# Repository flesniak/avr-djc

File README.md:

avr-djc
=======

Firmware for self-made MIDI DJ controller using AVR µC and V-USB

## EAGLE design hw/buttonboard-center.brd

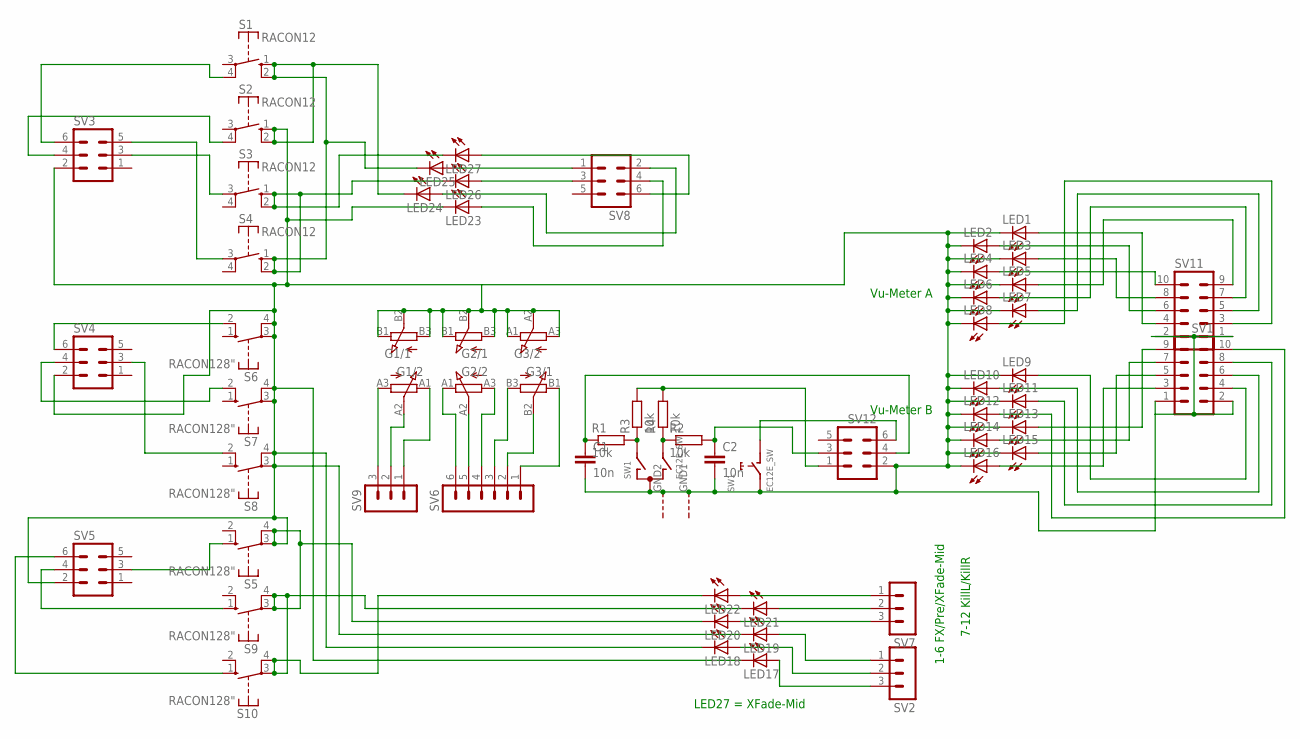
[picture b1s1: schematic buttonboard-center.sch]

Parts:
C1, C2: 10n; C025-025X050
G1, G2, G3: RS60112RS; RS60112
LED1, LED2, LED3, LED4, LED5, LED6, LED7, LED8, LED9, LED10, LED11, LED12, LED13, LED14, LED15, LED16, LED17, LED18, LED19, LED20, LED21, LED22, LED23, LED24, LED25, LED26, LED27: LED3MM
R1, R2, R3, R4: 10k; 0207/7
S1, S2, S3, S4: RACON12
S5, S6, S7, S8, S9, S10: RACON128"; RACON8
SV1, SV11: MA05-2
SV2, SV7, SV9: MA03-1
SV3, SV4, SV5, SV8, SV12: MA03-2
SV6: MA06-1
SW1: EC12E_SW; ALPS_EC12E_SW

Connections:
GND: C1.2, C2.2, G1.B1 (E), G1.B2 (S), G1.B3 (A), G2.B1 (E), G2.B2 (S), G2.B3 (A), G3.A1 (E), G3.A2 (S), G3.A3 (A), LED1.K (C), LED2.K (C), LED3.K (C), LED4.K (C), LED5.K (C), LED6.K (C), LED7.K (C), LED8.K (C), LED9.K (C), LED10.K (C), LED11.K (C), LED12.K (C), LED13.K (C), LED14.K (C), LED15.K (C), LED16.K (C), LED17.K (C), LED18.K (C), LED19.K (C), LED20.K (C), LED21.K (C), LED22.K (C), LED23.K (C), LED24.K (C), LED25.K (C), LED26.K (C), LED27.K (C), S1.1 (S), S1.2 (S), S2.1 (S), S2.2 (S), S3.1 (S), S3.2 (S), S4.1 (S), S4.2 (S), S5.3, S5.4, S6.3, S6.4, S7.3, S7.4, S8.3, S8.4, S9.3, S9.4, S10.3, S10.4, SV1.1, SV1.2, SV3.2, SV4.2, SV5.2, SV11.1, SV11.2, SV12.2, SW1.C, SW1.E (2), SW1.GND1 (G), SW1.GND2 (G)
unnamed: R1.2, R3.1, SW1.A
unnamed: LED16.A, SV1.3
unnamed: LED15.A, SV1.5
unnamed: LED14.A, SV1.7
unnamed: LED13.A, SV1.9
unnamed: LED12.A, SV1.10
unnamed: LED11.A, SV1.8
unnamed: LED10.A, SV1.6
unnamed: LED9.A, SV1.4
unnamed: LED8.A, SV11.3
unnamed: LED7.A, SV11.5
unnamed: LED6.A, SV11.7
unnamed: LED5.A, SV11.9
unnamed: LED4.A, SV11.10
unnamed: LED3.A, SV11.8
unnamed: R2.1, R4.1, SW1.B
unnamed: C1.1, R1.1, SV12.4
unnamed: LED2.A, SV11.6
unnamed: LED1.A, SV11.4
unnamed: LED17.A, SV2.3
unnamed: LED18.A, SV2.2
unnamed: LED19.A, SV2.1
unnamed: LED20.A, SV7.3
unnamed: LED21.A, SV7.2
unnamed: LED22.A, SV7.1
unnamed: LED24.A, SV8.2
unnamed: SV12.6, SW1.D (1)
unnamed: LED25.A, SV8.1
unnamed: S3.3, SV3.3
unnamed: LED23.A, SV8.4
unnamed: S2.4, SV3.4
unnamed: S1.4, SV3.6
unnamed: C2.1, R2.2, SV12.3
unnamed: R3.2, R4.2, SV12.1
unnamed: LED26.A, SV8.3
unnamed: S6.2 (S), SV4.6
unnamed: LED27.A, SV8.6
unnamed: S4.3, SV3.5
unnamed: S5.1 (S), SV5.3
unnamed: G1.A3 (A), SV9.3
unnamed: G1.A2 (S), SV9.2
unnamed: G1.A1 (E), SV9.1
unnamed: G2.A1 (E), SV6.6
unnamed: G2.A2 (S), SV6.5
unnamed: G2.A3 (A), SV6.4
unnamed: G3.B3 (A), SV6.3
unnamed: G3.B2 (S), SV6.2
unnamed: G3.B1 (E), SV6.1
unnamed: S9.1 (S), SV5.4
unnamed: S7.2 (S), SV4.4
unnamed: S8.2 (S), SV4.3
unnamed: S10.1 (S), SV5.6

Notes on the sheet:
Vu-Meter A
Vu-Meter B
LED27 = XFade-Mid
1-6 FX/Pre/XFade-Mid
7-12 KillL/KillR

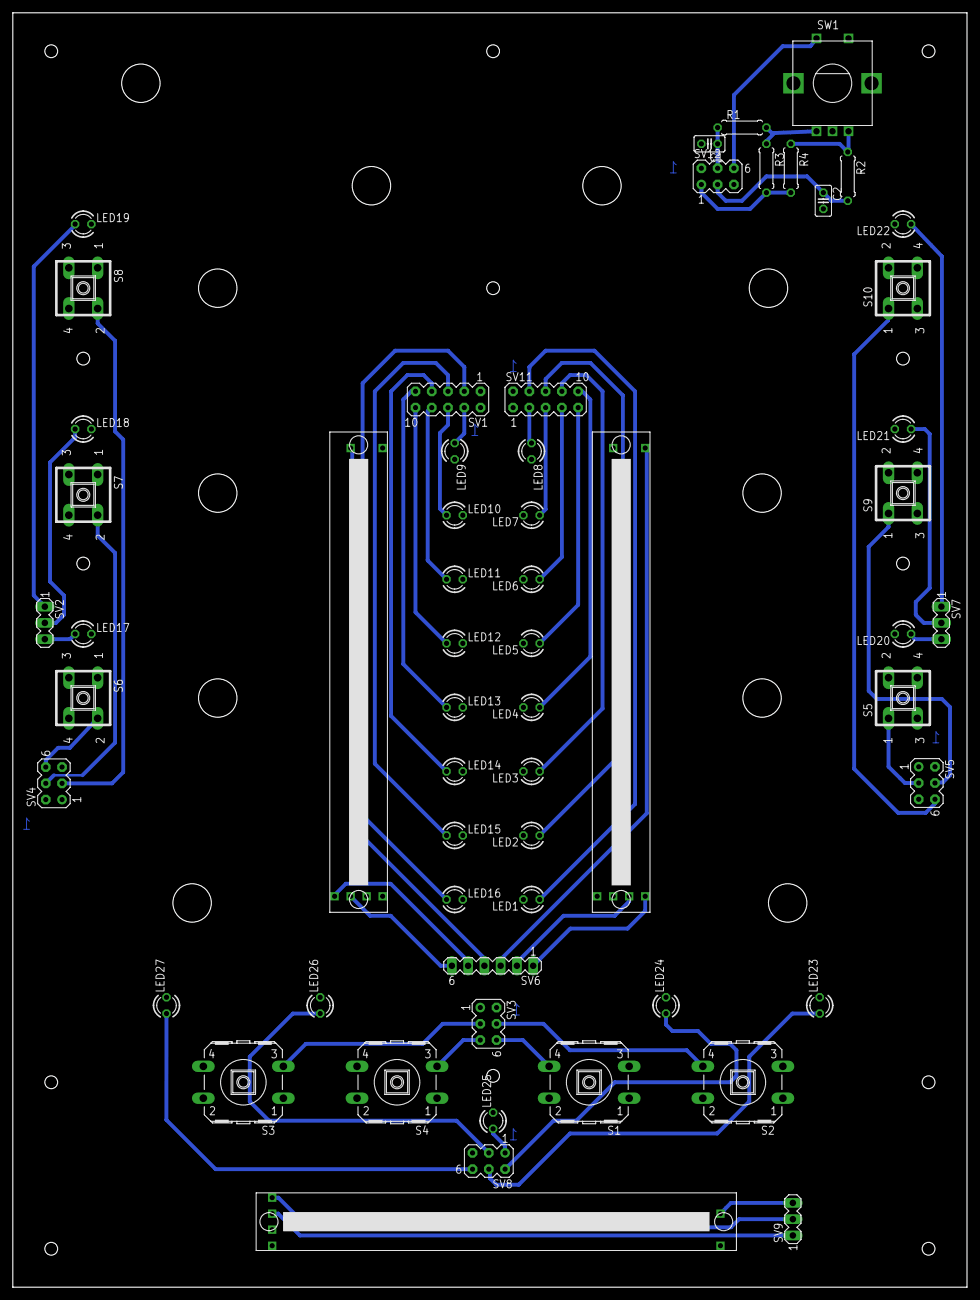
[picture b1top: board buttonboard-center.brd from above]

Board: 2 copper layers, 149.0 x 199.0 mm, 58 parts (0 on the bottom side), 53 nets.

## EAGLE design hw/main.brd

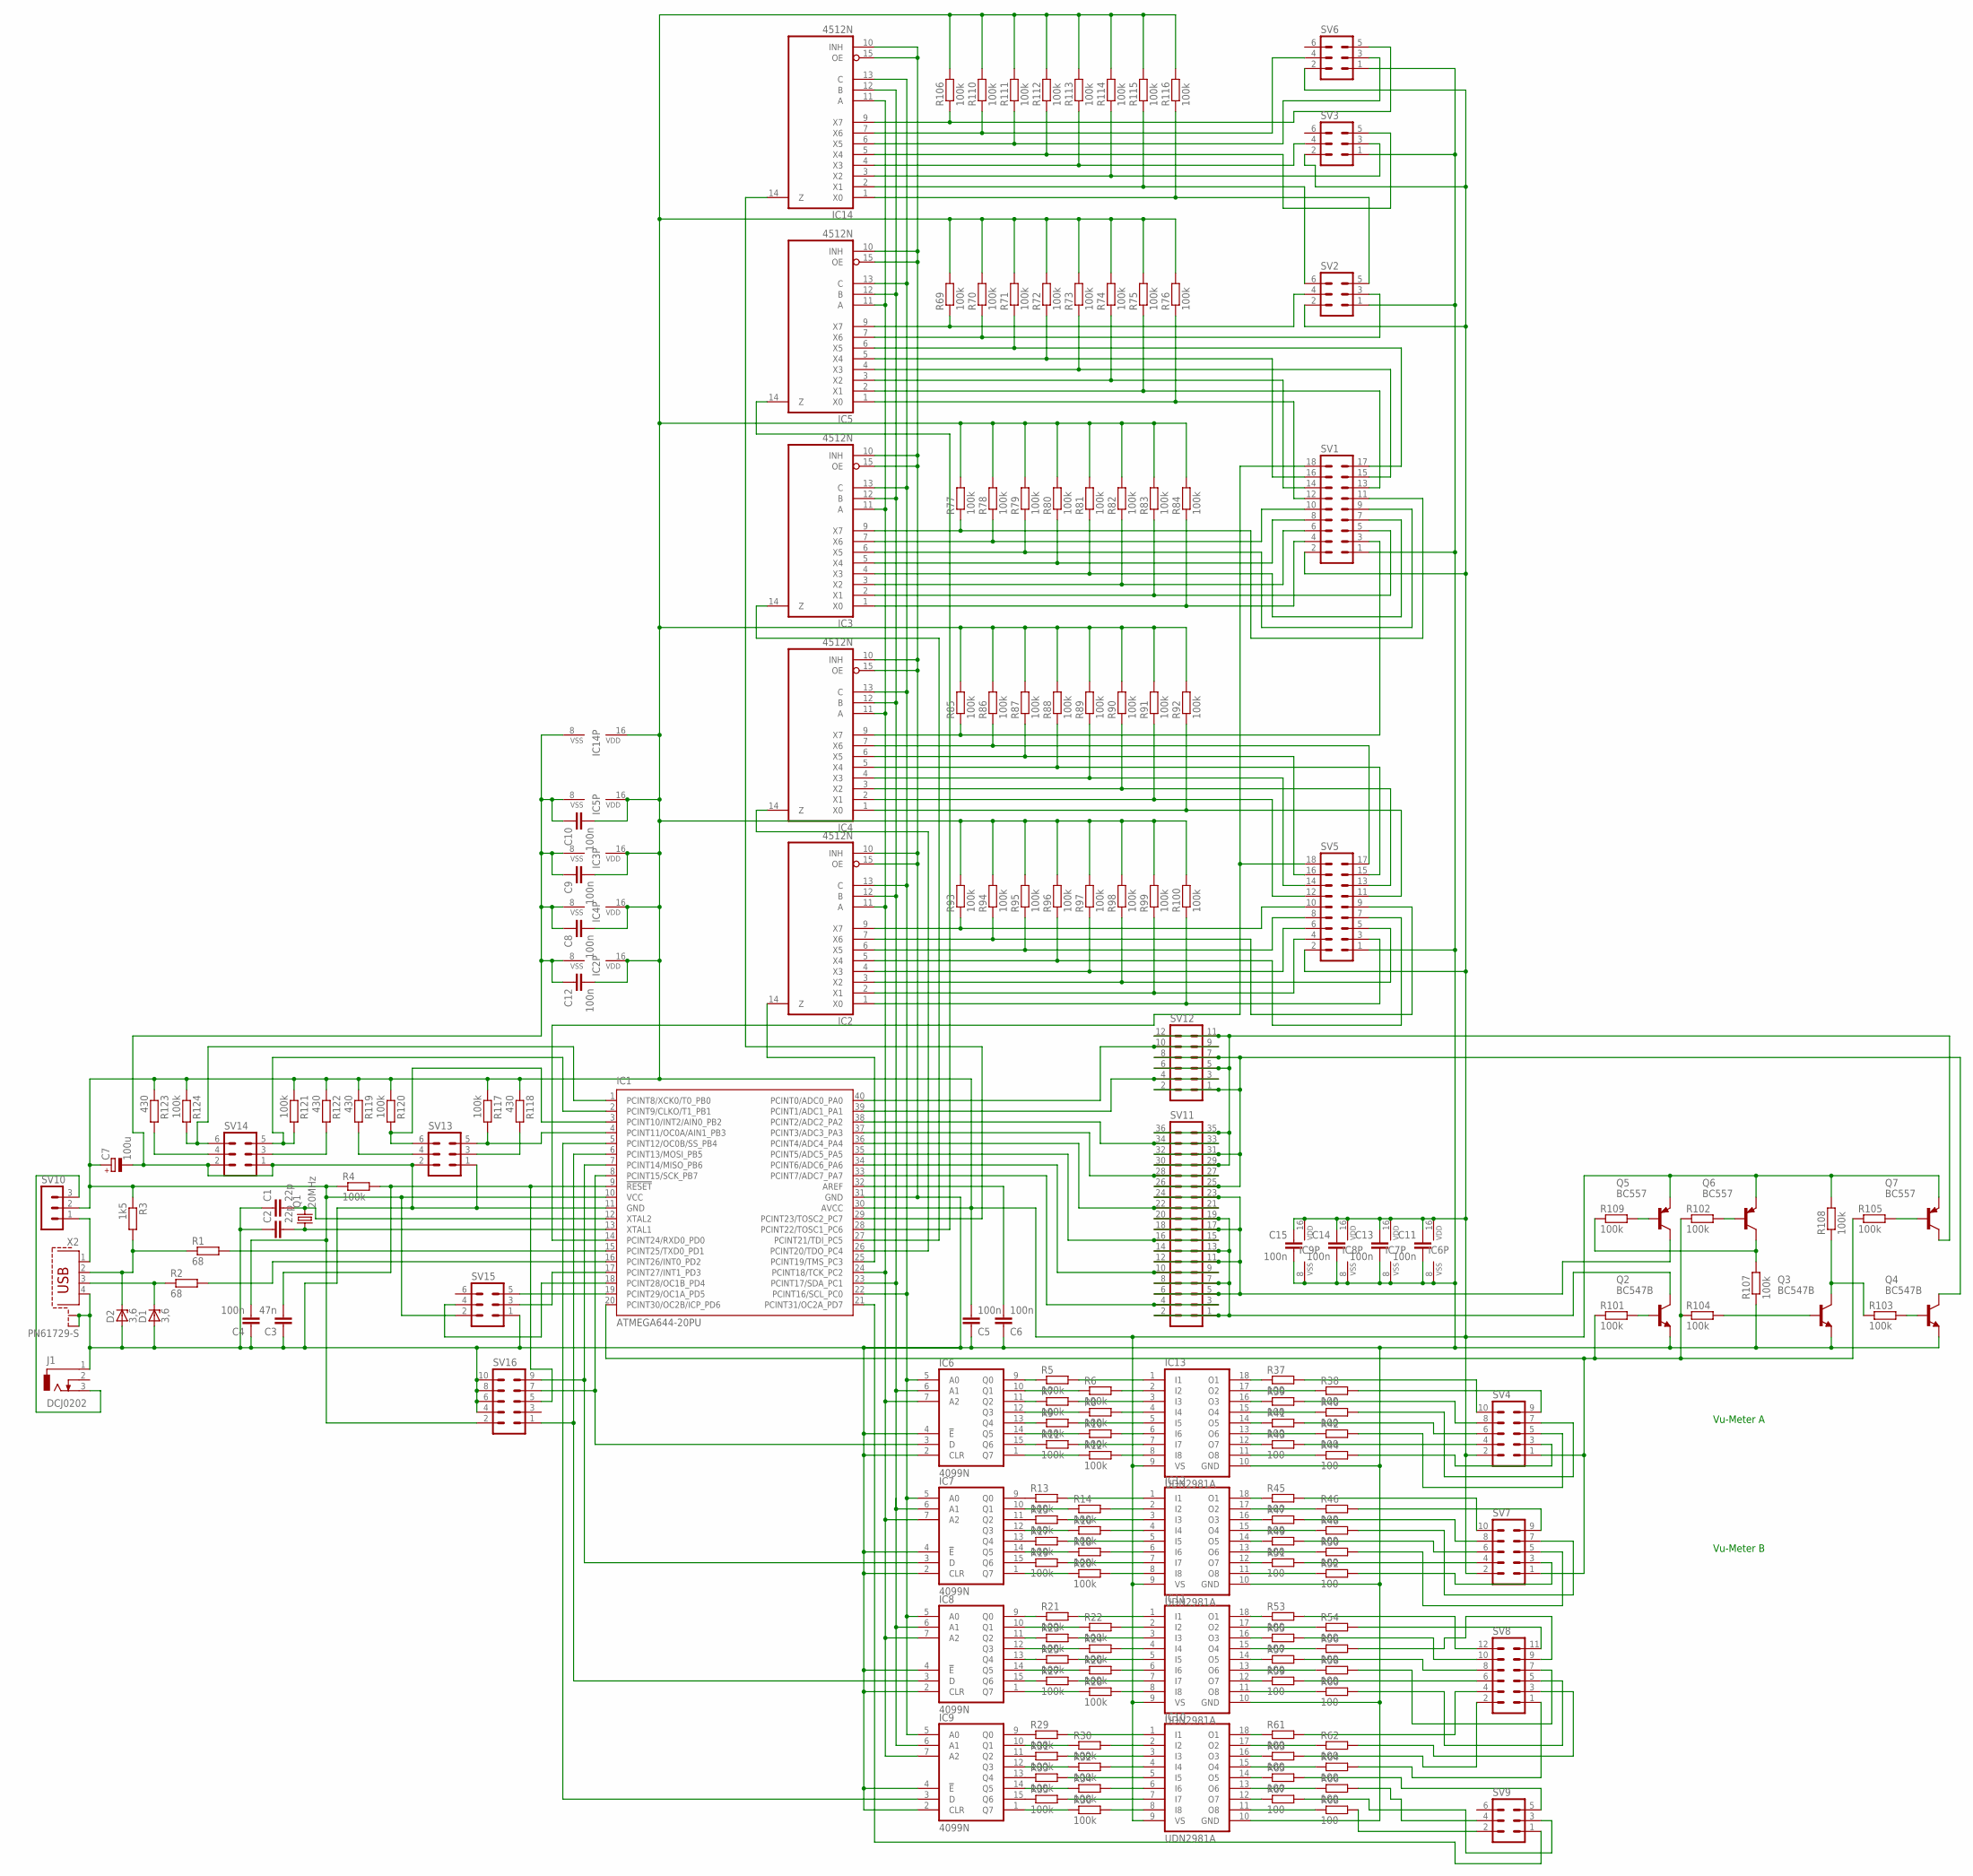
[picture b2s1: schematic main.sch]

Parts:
C1, C2: 22p; C025-024X044
C3: 47n; C025-024X044
C4, C5, C6, C8, C9, C10, C11, C12, C13, C14, C15: 100n; C025-024X044
C7: 100u; E3,5-8
D1, D2: 3,6; DO34Z7
IC1: ATMEGA644-20PU; DIL40
IC2, IC3, IC4, IC5, IC14: 4512N; DIL16
IC6, IC7, IC8, IC9: 4099N; DIL16
IC10, IC11, IC12, IC13: UDN2981A; DIL18
J1: DCJ0202
Q1: 20MHz; HC18U-V
Q2, Q3, Q4: BC547B; TO92
Q5, Q6, Q7: BC557; TO92
R1, R2: 68; 0204/7
R3: 1k5; 0204/7
R4, R5, R6, R7, R8, R9, R10, R11, R12, R13, R14, R15, R16, R17, R18, R19, R20, R21, R22, R23, R24, R25, R26, R27, R28, R29, R30, R31, R32, R33, R34, R35, R36, R69, R70, R71, R72, R73, R74, R75, R76, R77, R78, R79, R80, R81, R82, R83, R84, R85, R86, R87, R88, R89, R90, R91, R92, R93, R94, R95, R96, R97, R98, R99, R100, R101, R102, R103, R104, R105, R106, R107, R108, R109, R110, R111, R112, R113, R114, R115, R116, R117, R120, R121, R124: 100k; 0204/7
R37, R38, R39, R40, R41, R42, R43, R44, R45, R46, R47, R48, R49, R50, R51, R52, R53, R54, R55, R56, R57, R58, R59, R60, R61, R62, R63, R64, R65, R66, R67, R68: 100; 0204/7
R118, R119, R122, R123: 430; 0204/7
SV1, SV5: MA09-2
SV2, SV3, SV6, SV9, SV13, SV14, SV15: MA03-2
SV4, SV7, SV16: MA05-2
SV8, SV12: MA06-2
SV10: MA03-1
SV11: MA18-2
X2: PN61729-S

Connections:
GND: C1.1, C2.1, C3.1, C4.1, C5.1, C6.1, C7.-, C8.1, C9.1, C10.1, C11.2, C12.1, C13.2, C14.2, C15.2, D1.A, D2.A, IC1.11 (GND), IC1.31 (GND), IC2.8 (VSS), IC2.10 (INH), IC2.15 (OE), IC3.8 (VSS), IC3.10 (INH), IC3.15 (OE), IC4.8 (VSS), IC4.10 (INH), IC4.15 (OE), IC5.8 (VSS), IC5.10 (INH), IC5.15 (OE), IC6.2 (CLR), IC6.4 (!E), IC6.8 (VSS), IC7.2 (CLR), IC7.4 (!E), IC7.8 (VSS), IC8.2 (CLR), IC8.4 (!E), IC8.8 (VSS), IC9.2 (CLR), IC9.4 (!E), IC9.8 (VSS), IC10.10 (GND), IC11.10 (GND), IC12.10 (GND), IC13.10 (GND), IC14.8 (VSS), IC14.10 (INH), IC14.15 (OE), J1.1, Q2.1 (E), Q3.1 (E), Q4.1 (E), R107.1, SV1.1, SV2.1, SV3.1, SV5.1, SV6.1, SV13.1, SV13.2, SV14.1, SV14.2, SV15.1, SV16.4, SV16.6, SV16.8, SV16.10, X2.4, X2.S1, X2.S2
unnamed: IC4.9 (X7), R85.1, SV1.3
unnamed: C2.2, IC1.13 (XTAL1), Q1.1
unnamed: C1.2, IC1.12 (XTAL2), Q1.2
unnamed: IC1.14 (PCINT24/RXD0_PD0), SV1.18, SV5.18
unnamed: D1.C, R2.1, X2.3
unnamed: D2.C, R1.1, R3.2, X2.2
unnamed: IC1.16 (PCINT26/INT0_PD2), R2.2
unnamed: IC1.15 (PCINT25/TXD0_PD1), R1.2
unnamed: C3.2, IC1.9 (!RESET), R4.2, SV16.5
unnamed: IC7.9 (Q0), R13.1
unnamed: IC7.11 (Q2), R15.1
unnamed: C6.2, IC1.32 (AREF)
unnamed: IC7.13 (Q4), R17.1
unnamed: IC7.15 (Q6), R19.1
unnamed: IC1.6 (PCINT13/MOSI_PB5), IC8.3 (D), SV16.1
unnamed: IC1.5 (PCINT12/OC0B/SS_PB4), IC9.3 (D)
unnamed: IC1.23 (PCINT17/SDA_PC1), IC2.12 (B), IC3.12 (B), IC4.12 (B), IC5.12 (B), IC6.6 (A1), IC7.6 (A1), IC8.6 (A1), IC9.6 (A1), IC14.12 (B)
unnamed: IC1.22 (PCINT16/SCL_PC0), IC2.13 (C), IC3.13 (C), IC4.13 (C), IC5.13 (C), IC6.5 (A0), IC7.5 (A0), IC8.5 (A0), IC9.5 (A0), IC14.13 (C)
unnamed: IC1.24 (PCINT18/TCK_PC2), IC2.11 (A), IC3.11 (A), IC4.11 (A), IC5.11 (A), IC6.7 (A2), IC7.7 (A2), IC8.7 (A2), IC9.7 (A2), IC14.11 (A)
unnamed: IC8.9 (Q0), R21.1
unnamed: IC8.10 (Q1), R22.1
unnamed: IC8.11 (Q2), R23.1
unnamed: IC8.12 (Q3), R24.1
unnamed: IC1.27 (PCINT21/TDI_PC5), IC3.14 (Z)
unnamed: IC1.25 (PCINT19/TMS_PC3), IC2.14 (Z)
unnamed: IC3.6 (X5), R79.1, SV1.9
unnamed: IC3.9 (X7), R77.1, SV1.11
unnamed: IC12.12 (O7), R51.1
unnamed: IC8.13 (Q4), R25.1
unnamed: IC8.14 (Q5), R26.1
unnamed: IC8.15 (Q6), R27.1
unnamed: IC8.1 (Q7), R28.1
unnamed: IC13.8 (I8), R12.2
unnamed: IC13.7 (I7), R11.2
unnamed: IC13.6 (I6), R10.2
unnamed: IC13.5 (I5), R9.2
unnamed: IC13.4 (I4), R8.2
unnamed: IC13.3 (I3), R7.2
unnamed: IC13.2 (I2), R6.2
unnamed: IC13.1 (I1), R5.2
unnamed: IC10.1 (I1), R29.2
unnamed: IC10.2 (I2), R30.2
unnamed: IC10.3 (I3), R31.2
unnamed: IC10.4 (I4), R32.2
unnamed: IC10.5 (I5), R33.2
unnamed: IC10.6 (I6), R34.2
unnamed: IC10.7 (I7), R35.2
unnamed: IC10.8 (I8), R36.2
unnamed: IC9.10 (Q1), R30.1
unnamed: IC9.12 (Q3), R32.1
unnamed: IC9.14 (Q5), R34.1
unnamed: IC9.1 (Q7), R36.1
unnamed: IC11.1 (I1), R21.2
unnamed: IC9.9 (Q0), R29.1
unnamed: IC9.11 (Q2), R31.1
unnamed: IC1.28 (PCINT22/TOSC1_PC6), IC5.14 (Z)
unnamed: IC1.26 (PCINT20/TDO_PC4), IC4.14 (Z)
unnamed: IC9.13 (Q4), R33.1
unnamed: IC11.2 (I2), R22.2
unnamed: IC9.15 (Q6), R35.1
unnamed: IC11.3 (I3), R23.2
unnamed: IC11.4 (I4), R24.2
unnamed: IC1.8 (PCINT15/SCK_PB7), IC6.3 (D), SV16.7
unnamed: IC1.7 (PCINT14/MISO_PB6), IC7.3 (D), SV16.9
unnamed: IC11.5 (I5), R25.2
unnamed: IC11.6 (I6), R26.2
unnamed: IC11.7 (I7), R27.2
unnamed: IC6.9 (Q0), R5.1
unnamed: IC6.10 (Q1), R6.1
unnamed: IC6.11 (Q2), R7.1
unnamed: IC6.12 (Q3), R8.1
unnamed: IC6.13 (Q4), R9.1
unnamed: IC6.14 (Q5), R10.1
unnamed: IC6.15 (Q6), R11.1
unnamed: IC6.1 (Q7), R12.1
unnamed: IC11.8 (I8), R28.2
unnamed: IC13.18 (O1), R37.1
unnamed: IC13.17 (O2), R38.1
unnamed: R37.2, SV4.10
unnamed: R38.2, SV4.9
unnamed: IC5.9 (X7), R69.1, SV2.4
unnamed: R53.2, SV8.12
unnamed: R39.2, SV4.8
unnamed: IC12.1 (I1), R13.2
unnamed: IC12.2 (I2), R14.2
unnamed: IC12.3 (I3), R15.2
unnamed: IC12.4 (I4), R16.2
unnamed: IC12.5 (I5), R17.2
unnamed: IC12.6 (I6), R18.2
unnamed: IC12.7 (I7), R19.2
unnamed: IC12.8 (I8), R20.2
unnamed: IC7.10 (Q1), R14.1
unnamed: IC7.12 (Q3), R16.1
unnamed: IC13.16 (O3), R39.1
unnamed: IC13.15 (O4), R40.1
unnamed: R40.2, SV4.7
unnamed: R41.2, SV4.6
unnamed: IC5.6 (X5), R71.1, SV1.17
unnamed: IC7.14 (Q5), R18.1
unnamed: IC7.1 (Q7), R20.1
unnamed: IC3.4 (X3), R81.1, SV1.7
unnamed: IC13.14 (O5), R41.1
unnamed: IC13.13 (O6), R42.1
unnamed: R42.2, SV4.5
unnamed: R43.2, SV4.4
unnamed: IC5.4 (X3), R73.1, SV1.15
unnamed: IC3.2 (X1), R83.1, SV1.5
unnamed: IC13.12 (O7), R43.1
unnamed: IC13.11 (O8), R44.1
unnamed: IC12.13 (O6), R50.1
unnamed: IC5.2 (X1), R75.1, SV1.13
unnamed: R54.2, SV8.11
unnamed: IC3.3 (X2), R82.1, SV1.6
unnamed: IC12.18 (O1), R45.1
unnamed: IC12.17 (O2), R46.1
unnamed: R44.2, SV4.3
unnamed: J1.3, SV10.3
unnamed: IC12.16 (O3), R47.1
unnamed: IC12.15 (O4), R48.1
unnamed: R45.2, SV7.10
unnamed: R46.2, SV7.9
unnamed: IC12.14 (O5), R49.1
unnamed: IC11.12 (O7), R59.1
unnamed: R47.2, SV7.8
unnamed: R48.2, SV7.7
unnamed: R55.2, SV8.10
unnamed: R49.2, SV7.6
unnamed: R50.2, SV7.5
unnamed: IC12.11 (O8), R52.1
unnamed: R51.2, SV7.4
unnamed: IC11.18 (O1), R53.1
unnamed: IC11.17 (O2), R54.1
unnamed: R52.2, SV7.3
unnamed: IC5.7 (X6), R70.1, SV2.3
unnamed: IC11.16 (O3), R55.1
unnamed: IC11.15 (O4), R56.1
unnamed: IC1.33 (PCINT7/ADC7_PA7), SV11.3, SV11.4
unnamed: IC3.1 (X0), R84.1, SV1.4
unnamed: IC11.14 (O5), R57.1
unnamed: IC11.13 (O6), R58.1
unnamed: R56.2, SV8.9
unnamed: R57.2, SV8.8
unnamed: R58.2, SV8.7
unnamed: R59.2, SV8.6
unnamed: R60.2, SV8.5
unnamed: IC11.11 (O8), R60.1
unnamed: R61.2, SV8.4
unnamed: IC10.18 (O1), R61.1
unnamed: IC10.17 (O2), R62.1
unnamed: R62.2, SV8.3
unnamed: IC1.34 (PCINT6/ADC6_PA6), SV11.9, SV11.10
unnamed: IC10.16 (O3), R63.1
unnamed: IC10.15 (O4), R64.1
unnamed: IC4.7 (X6), R86.1, SV5.17
unnamed: IC4.6 (X5), R87.1, SV5.16
unnamed: IC10.14 (O5), R65.1
unnamed: IC10.13 (O6), R66.1
unnamed: IC4.5 (X4), R88.1, SV5.15
unnamed: IC4.4 (X3), R89.1, SV5.14
unnamed: IC10.12 (O7), R67.1
unnamed: IC4.3 (X2), R90.1, SV5.13
unnamed: IC1.29 (PCINT23/TOSC2_PC7), IC14.14 (Z)
unnamed: IC10.11 (O8), R68.1
unnamed: IC5.5 (X4), R72.1, SV1.16
unnamed: IC4.2 (X1), R91.1, SV5.12
unnamed: R63.2, SV8.2
unnamed: IC4.1 (X0), R92.1, SV5.11
unnamed: IC2.9 (X7), R93.1, SV5.10
unnamed: IC2.7 (X6), R94.1, SV5.9
unnamed: IC2.6 (X5), R95.1, SV5.8
unnamed: IC14.9 (X7), R106.1, SV6.5
unnamed: IC2.5 (X4), R96.1, SV5.7
unnamed: IC14.7 (X6), R110.1, SV6.4
unnamed: IC14.6 (X5), R111.1, SV6.3
unnamed: IC14.4 (X3), R113.1, SV3.4
unnamed: IC14.2 (X1), R115.1, SV2.6
unnamed: IC2.4 (X3), R97.1, SV5.6
unnamed: IC2.3 (X2), R98.1, SV5.5
unnamed: R64.2, SV8.1
unnamed: IC2.2 (X1), R99.1, SV5.4
unnamed: R65.2, SV9.5
unnamed: IC2.1 (X0), R100.1, SV5.3
unnamed: R66.2, SV9.4
unnamed: IC3.7 (X6), R78.1, SV1.10
unnamed: IC1.20 (PCINT30/OC2B/ICP_PD6), R101.1, R102.1, R104.1, R105.1, SV4.1, SV7.1
unnamed: Q6.2 (B), R102.2
unnamed: R67.2, SV9.3
unnamed: IC14.5 (X4), R112.1, SV3.5
unnamed: Q7.2 (B), R105.2
unnamed: IC14.3 (X2), R114.1, SV3.3
unnamed: IC14.1 (X0), R116.1, SV2.5
unnamed: Q2.2 (B), R101.2
unnamed: R68.2, SV9.2
unnamed: IC3.5 (X4), R80.1, SV1.8
unnamed: Q3.2 (B), R104.2
unnamed: Q6.3 (C), R107.2, R109.1
unnamed: Q3.3 (C), R103.1, R108.1
unnamed: Q4.2 (B), R103.2
unnamed: Q5.2 (B), R109.2
unnamed: IC1.21 (PCINT31/OC2A_PD7), SV9.1
unnamed: IC1.4 (PCINT11/OC0A/AIN1_PB3), R117.2, SV13.5
unnamed: R118.2, SV13.3
unnamed: IC1.3 (PCINT10/INT2/AIN0_PB2), R120.2, SV13.6
unnamed: IC1.35 (PCINT5/ADC5_PA5), SV11.15, SV11.16
unnamed: R119.2, SV13.4
unnamed: IC1.2 (PCINT9/CLKO/T1_PB1), R121.2, SV14.5
unnamed: R122.2, SV14.3
unnamed: IC1.1 (PCINT8/XCK0/T0_PB0), R124.2, SV14.6
unnamed: SV10.1, X2.1
unnamed: IC1.36 (PCINT4/ADC4_PA4), SV11.21, SV11.22
unnamed: IC1.37 (PCINT3/ADC3_PA3), SV11.27, SV11.28
unnamed: R123.2, SV14.4
unnamed: IC1.38 (PCINT2/ADC2_PA2), SV11.33, SV11.34
unnamed: IC5.3 (X2), R74.1, SV1.14
unnamed: IC1.39 (PCINT1/ADC1_PA1), SV12.3, SV12.4
unnamed: IC5.1 (X0), R76.1, SV1.12
unnamed: IC1.40 (PCINT0/ADC0_PA0), SV12.9, SV12.10
unnamed: Q4.3 (C), SV11.25, SV11.26, SV11.31, SV11.32, SV12.1, SV12.2, SV12.7, SV12.8
unnamed: IC1.18 (PCINT28/OC1B_PD4), SV15.4
unnamed: IC1.19 (PCINT29/OC1A_PD5), SV15.5
unnamed: IC1.17 (PCINT27/INT1_PD3), SV15.3
unnamed: Q5.3 (C), SV11.5, SV11.6, SV11.11, SV11.12, SV11.17, SV11.18, SV11.23, SV11.24
unnamed: Q2.3 (C), SV11.1, SV11.2, SV11.7, SV11.8, SV11.13, SV11.14, SV11.19, SV11.20
unnamed: Q7.3 (C), SV11.29, SV11.30, SV11.35, SV11.36, SV12.5, SV12.6, SV12.11, SV12.12
VCC: C4.2, C5.2, C7.+, C8.2, C9.2, C10.2, C11.1, C12.2, C13.1, C14.1, C15.1, IC1.10 (VCC), IC1.30 (AVCC), IC2.16 (VDD), IC3.16 (VDD), IC4.16 (VDD), IC5.16 (VDD), IC6.16 (VDD), IC7.16 (VDD), IC8.16 (VDD), IC9.16 (VDD), IC10.9 (VS), IC11.9 (VS), IC12.9 (VS), IC13.9 (VS), IC14.16 (VDD), Q5.1 (E), Q6.1 (E), Q7.1 (E), R3.1, R4.1, R69.2, R70.2, R71.2, R72.2, R73.2, R74.2, R75.2, R76.2, R77.2, R78.2, R79.2, R80.2, R81.2, R82.2, R83.2, R84.2, R85.2, R86.2, R87.2, R88.2, R89.2, R90.2, R91.2, R92.2, R93.2, R94.2, R95.2, R96.2, R97.2, R98.2, R99.2, R100.2, R106.2, R108.2, R110.2, R111.2, R112.2, R113.2, R114.2, R115.2, R116.2, R117.1, R118.1, R119.1, R120.1, R121.1, R122.1, R123.1, R124.1, SV1.2, SV2.2, SV3.2, SV4.2, SV5.2, SV6.2, SV7.2, SV10.2, SV15.2, SV16.2

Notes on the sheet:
Vu-Meter A
Vu-Meter B

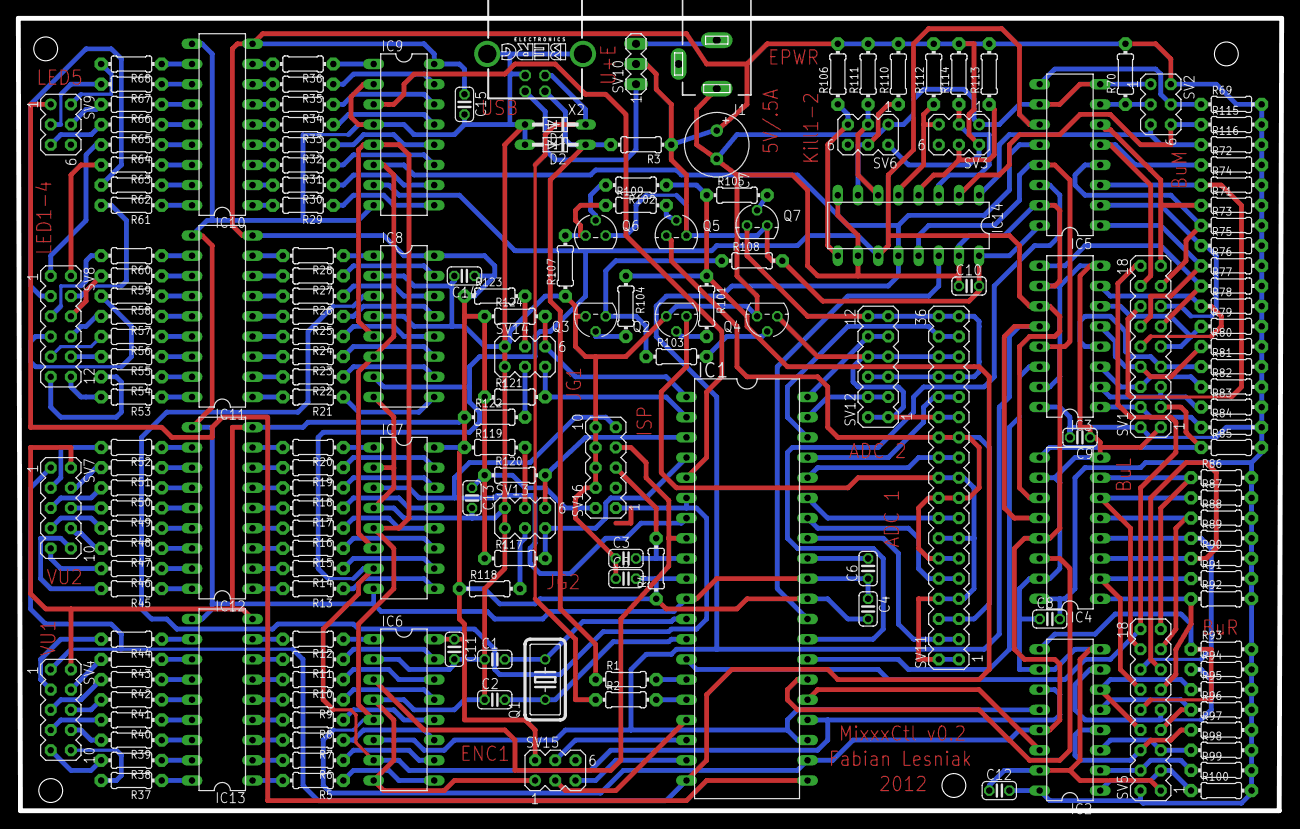
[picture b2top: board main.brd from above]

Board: 2 copper layers, 159.0 x 99.7 mm, 180 parts (0 on the bottom side), 226 nets.

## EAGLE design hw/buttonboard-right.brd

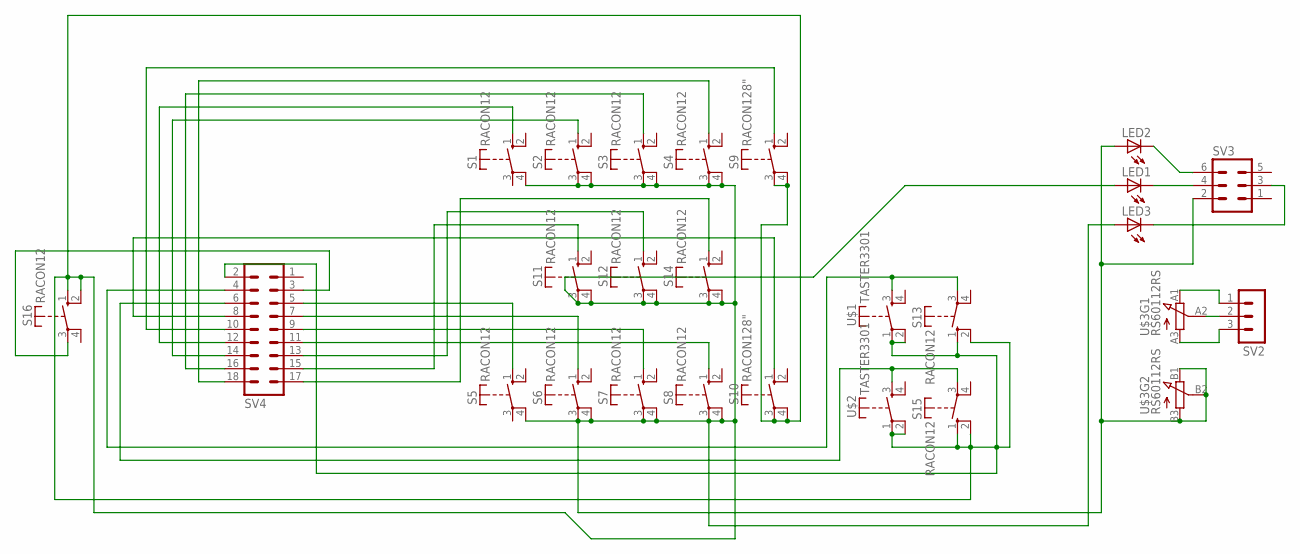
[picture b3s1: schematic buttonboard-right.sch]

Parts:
LED1, LED2, LED3: LED3MM
S1, S2, S3, S4, S5, S6, S7, S8, S11, S12, S13, S14, S15, S16: RACON12
S9, S10: RACON128"; RACON8
SV2: MA03-1
SV3: MA03-2
SV4: MA09-2
U$1, U$2: TASTER3301; 3301
U$3: RS60112RS; RS60112

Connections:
GND: LED1.A, LED2.A, LED3.A, S1.4, S2.3, S2.4, S3.3, S3.4, S4.3, S4.4, S5.4, S6.3, S6.4, S7.3, S7.4, S8.3, S8.4, S9.3, S9.4, S10.3, S10.4, S11.3, S11.4, S12.3, S12.4, S13.1 (S), S13.2 (S), S14.3, S14.4, S15.1 (S), S15.2 (S), S16.1 (S), S16.2 (S), SV3.2, SV4.2, U$1.1, U$1.2, U$2.1, U$2.2, U$3.B1 (E), U$3.B2 (S), U$3.B3 (A)
unnamed: S10.1 (S), SV4.8
unnamed: S1.1 (S), SV4.12
unnamed: S6.1 (S), SV4.7
unnamed: S2.1 (S), SV4.14
unnamed: S7.1 (S), SV4.9
unnamed: S8.1 (S), SV4.11
unnamed: S5.1 (S), SV4.5
unnamed: S15.3, SV4.6, U$2.3 (S)
unnamed: S3.1 (S), SV4.16
unnamed: S13.3, SV4.4, U$1.3 (S)
unnamed: LED2.K (C), SV3.6
unnamed: LED1.K (C), SV3.4
unnamed: LED3.K (C), SV3.3
unnamed: S4.1 (S), SV4.18
unnamed: SV2.2, U$3.A2 (S)
unnamed: SV2.1, U$3.A1 (E)
unnamed: SV2.3, U$3.A3 (A)
unnamed: S16.3, SV4.3
unnamed: S12.1 (S), SV4.13
unnamed: S9.1 (S), SV4.10
unnamed: S11.1 (S), SV4.15
unnamed: S14.1 (S), SV4.17

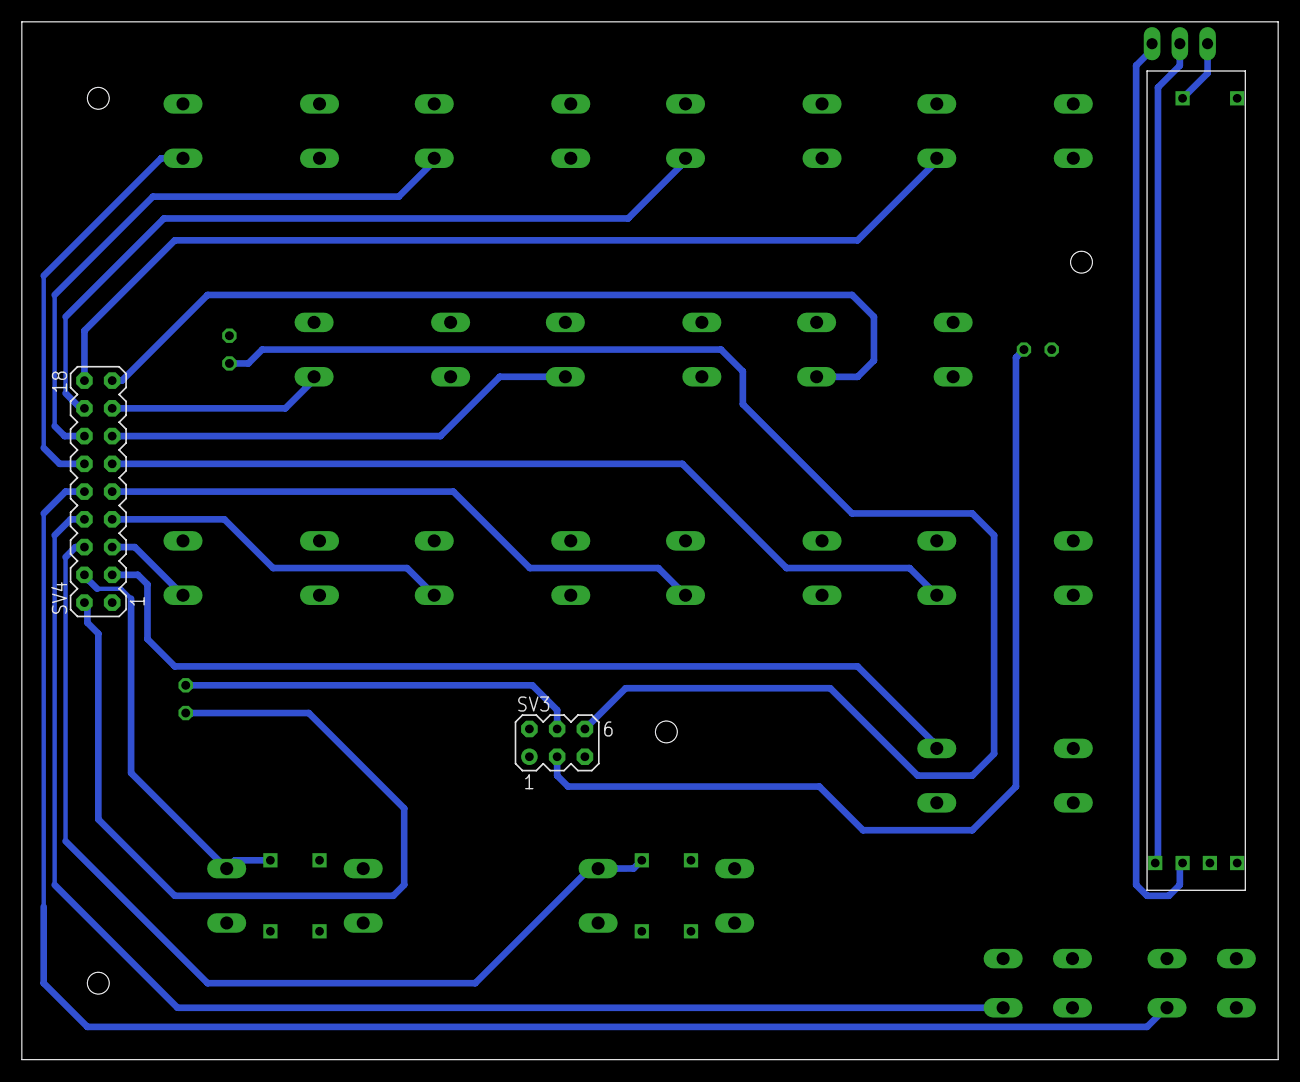
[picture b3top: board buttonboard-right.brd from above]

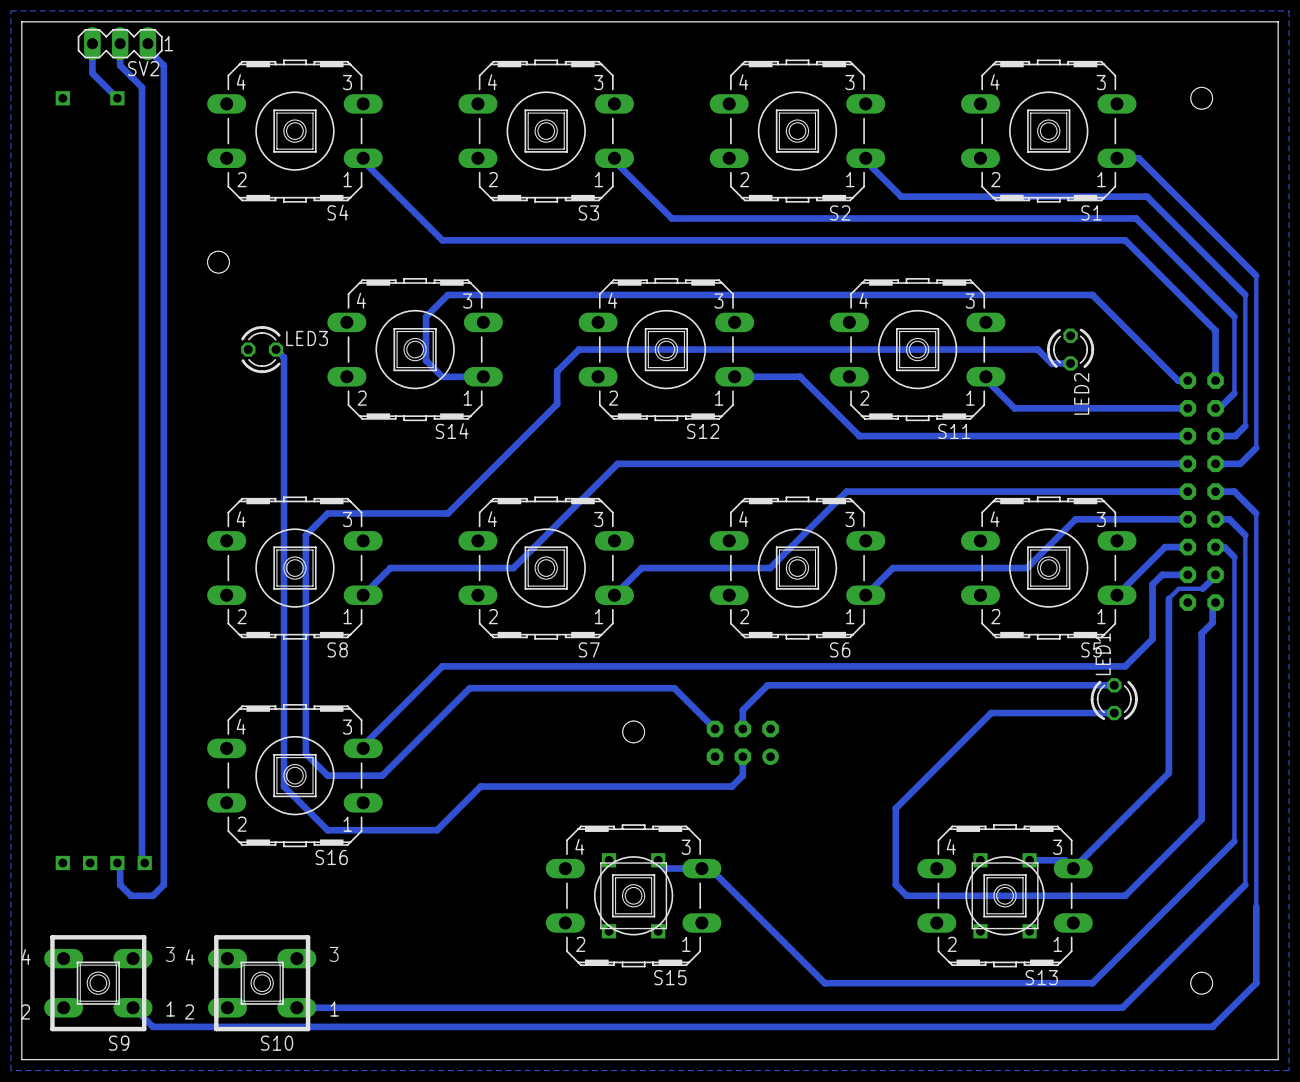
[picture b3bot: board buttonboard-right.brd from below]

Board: 2 copper layers, 115.0 x 95.0 mm, 25 parts (22 on the bottom side), 23 nets.

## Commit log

2012-07-12 lot of stuff done
2012-07-12 stuff laptop
2012-07-14 newline at end of file
2012-07-14 portd pullup resistors fixed
2012-07-14 interrupt-triggering for encoder
2012-08-24 audiointerface chips
2012-09-28 status commit
2013-01-16 moved from ADCCHANGE to LWENABLE/DISABLE macros
    now the led latches' WRITE DISABLE resides on PD6
2013-01-29 ADC conversion updated to changed layout
2013-01-29 buttons, convenient leds, pots working
2013-01-30 xfade led working well
2013-01-30 ids remapped, vumeter-at-once-control added, cleanup
2013-01-31 few fixed + extra files
    -mixxx mappings added
    -led test script added
    -few bugfixes in firmware
2013-02-02 4-step vumeters test
2013-05-09 4-state vu led logic fix
2013-05-14 harddisk jog wheel test
2013-05-15 jog wheel fix
    removed mapping links
    compile script updated
2013-05-15 julius' implementation of jog algorithm
2013-06-11 code cleanup
2014-07-09 added case front plane
2014-11-17 added makefile
    fixed usbdrv for newer gcc
    removed old compile script
2015-09-24 first final, fully working version
    + re-worked jogwheel code
    + re-worked soft-pwm for vu
    + implemented sysex handling
    + added protocol documentation
    + enhanced makefile
2015-10-12 added mappings and protocol description
    - added mixxx mappings
    - added protocol description
    - improved led test script
    - removed outdated traktor layout
2015-10-15 improved mixxx mapping
2016-05-06 updated mixxx mapping
2020-02-23 add schematic and board files of prototype
    Beware that these files may contain errors and should be used for
    referene only.
